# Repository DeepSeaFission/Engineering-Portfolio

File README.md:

# Engineering Portfolio - Jordan Langford

This repository contains my current engineering portfolio, including my work on power distribution system for a 1U Cubesat as the Team Lead for the University of Utah's UCubeSat Photovoltaics and Power Distribution team, a custom GPS personal project, and code demosntrating my use of complex boolean statements, GUI generation, and machine learning techniques.

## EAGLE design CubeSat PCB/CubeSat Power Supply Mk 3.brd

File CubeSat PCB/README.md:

# 1U CubeSat Power Supply - UCubeSat Collegiate Club Activity
Generated as Team Lead for the Photovoltaics and Power Distribution Team

This project was my attempt to produce a reliable 1U CubeSat Power Supply powered by two Li-Po 18650 batteries. 

## Mk 1

This PCB went through several iterations before reaching this final stage. Initially, when the UCubeSat club was just getting started and our requirements were ill-defined, I began with a dual 12V/5V power supply just to have something for the team to work on and to generate interest. That design included a boost converter to generate the 12V, since the combined voltage of the 18650 batteries was only around 8.4V at max charge. 

## Mk 2

After further design refining, we determined only a 5V rail was necessary. Intead of a buck converter that would need to operate at high efficiency across the full range of voltage the batteries would produce in series, I opted for a design relying on voltage following OpAmps following a stable 5V positive terminal voltage generated by a zener diode. The zener diode branch draws low current thanks to high resistance resistors in series with the diode. 

Unfortunately, my first iteration of this design had a few flaws. I wired the Opamp outputs together with the intention of having a combined source of power. When simulated in LTspice, this seemed to work well. However, in practice, this led to the feedback loops for each OpAmp fighting, leading to rapid overheating and failure. I also was attempting to solder USB-C ports to the PCB, which is extremely difficult to do by hand.

## Mk 3

This led to my final iteration. 

Each OpAmp was given a dedicated output line with an RLC filter, supplying 1 Amp at 5V. The connectors were removed with the intention that any power taps would just be soldered directly to the board using vias. This iteration is capable of powering every load we have planned for several hours. In the future, we believe it will require minimal modification to work with a solar power supply for recharging. 

This screenshot shows the traces for the PCB. High current traces are 2 mm thickness, most control traces are 0.2 mm.

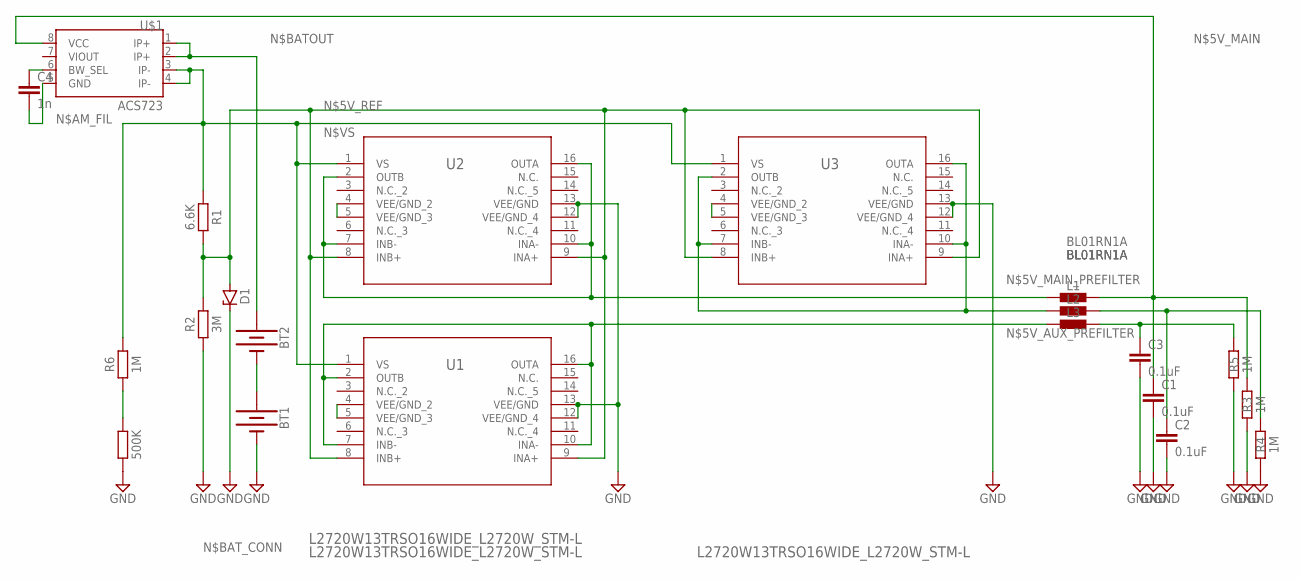
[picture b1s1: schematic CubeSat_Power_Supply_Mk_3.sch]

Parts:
BT1, BT2: BATTERY-18650; BATTERY_18650-HOLDER
C1, C2, C3: 0.1uF; CAP-PTH-SMALL-KIT
C4: 1n; CAP-PTH-SMALL-KIT
D1: ZENER-DIODESOT23; SOT23
L1, L2, L3: BL01RN1A
R1: 6.6K; RESAD724W46L381D178B
R2: 3M; RESAD724W46L381D178B
R3, R4, R5, R6: 1M; RESAD724W46L381D178B
R7: 500K; RESAD724W46L381D178B
U1, U2, U3: L2720W13TRSO16WIDE_L2720W_STM-L; SO16WIDE_L2720W_STM-L
U$1: ACS723; SO08

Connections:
GND: BT1.GND@1 (-), C1.2, C2.2, C3.2, D1.3 (C), R2.1, R3.1, R4.1, R5.1, R7.1, U1.12 (VEE/GND_4), U1.13 (VEE/GND), U2.12 (VEE/GND_4), U2.13 (VEE/GND), U3.12 (VEE/GND_4), U3.13 (VEE/GND)
unnamed: U2.4 (VEE/GND_2), U2.5 (VEE/GND_3)
unnamed: U1.4 (VEE/GND_2), U1.5 (VEE/GND_3)
unnamed: U3.4 (VEE/GND_2), U3.5 (VEE/GND_3)
unnamed: L3.1, U1.2 (OUTB), U1.7 (INB-), U1.10 (INA-), U1.16 (OUTA)
unnamed: C3.1, L3.2, R5.2
unnamed: C2.1, L2.2, R4.2
unnamed: L2.1, U3.2 (OUTB), U3.7 (INB-), U3.10 (INA-), U3.16 (OUTA)
unnamed: C1.1, L1.2, R3.2, U$1.8 (VCC)
unnamed: L1.1, U2.2 (OUTB), U2.7 (INB-), U2.10 (INA-), U2.16 (OUTA)
unnamed: D1.1 (A), R1.2, R2.2, U1.8 (INB+), U1.9 (INA+), U2.8 (INB+), U2.9 (INA+), U3.8 (INB+), U3.9 (INA+)
unnamed: C4.2, U$1.5 (GND)
N$AM_FIL: C4.1, U$1.6 (BW_SEL)
N$BATOUT: BT2.PWR@1 (+), U$1.1 (IP+), U$1.2 (IP+)
N$BAT_CONN: BT1.PWR@1 (+), BT2.GND@1 (-)
N$VMSUP: R6.1, R7.2
N$VS: R1.1, R6.2, U1.1 (VS), U2.1 (VS), U3.1 (VS), U$1.3 (IP-), U$1.4 (IP-)

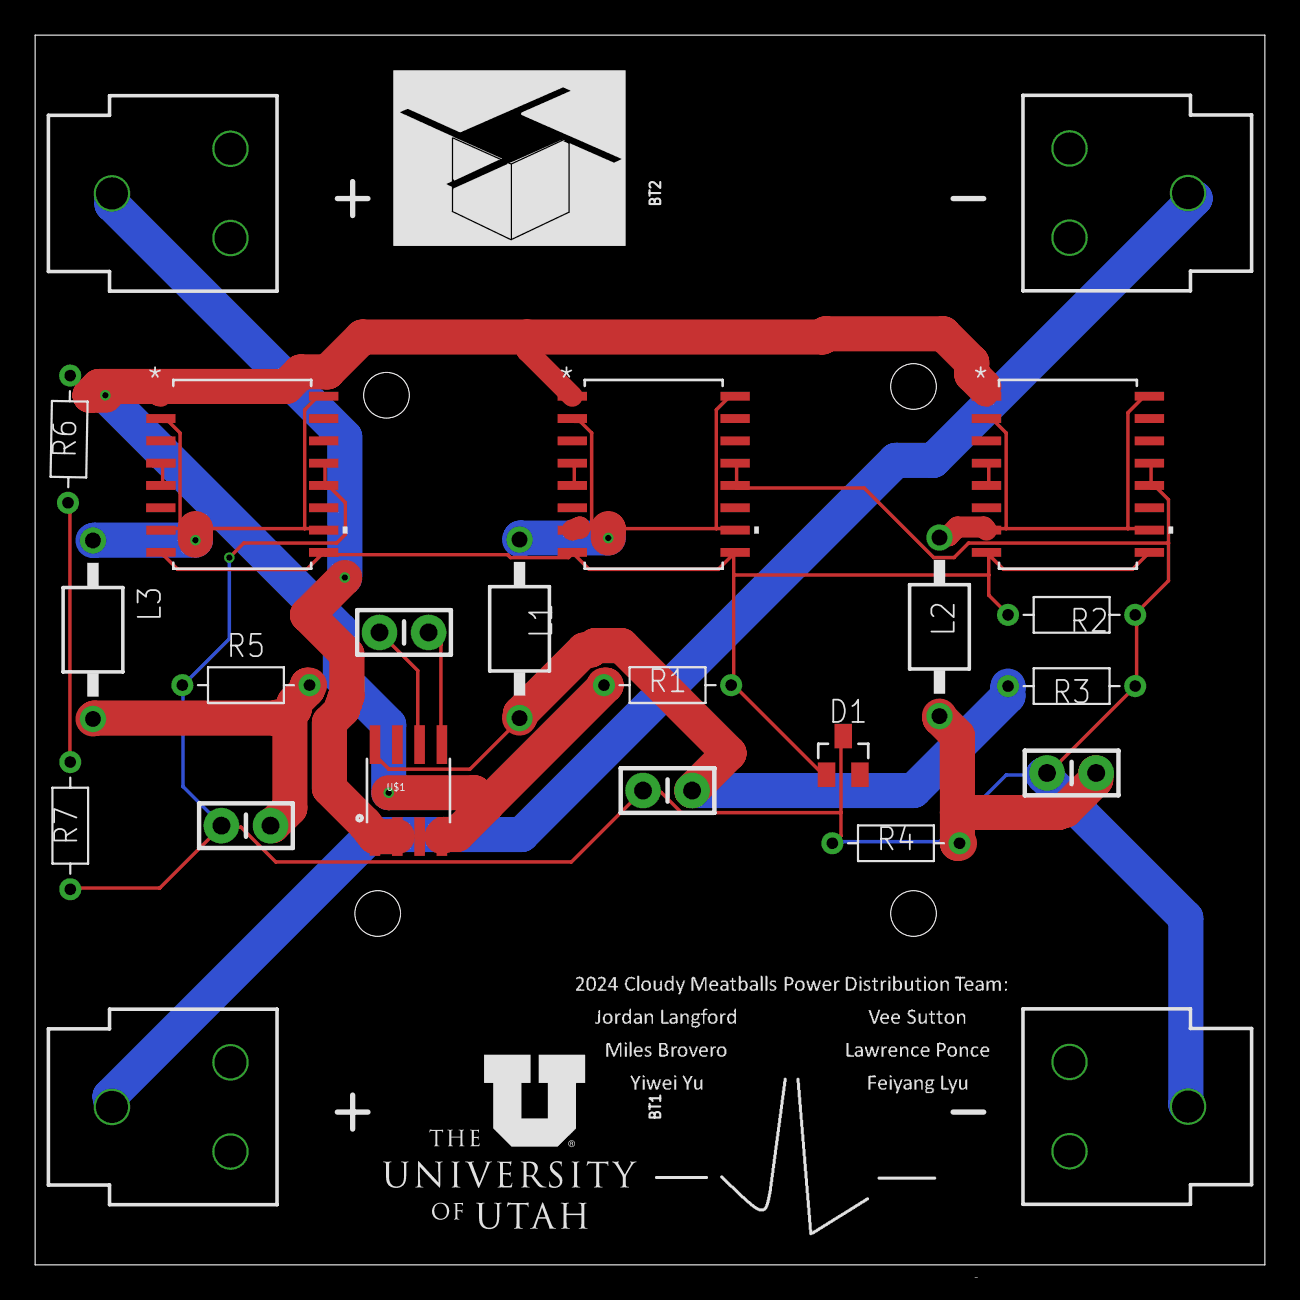
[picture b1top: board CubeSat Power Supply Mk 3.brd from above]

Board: 2 copper layers, 70.0 x 70.0 mm, 21 parts (0 on the bottom side), 17 nets.

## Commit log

2026-05-05 Added CubeSat Project Files
    CubeSat Power Supply Mk 3 files added. This is the initial release of my cubesat power supply, providing three regulated and filtered 1A 5V rails.
2026-05-05 CubeSat PS Screenshots
    Adding screenshots for use in the README
2026-05-05 Add README for CubeSat PCB power supply project
    Document the design process and iterations of the CubeSat PCB power supply project, including images of the final PCB, schematic, and traces.
2026-05-05 Revise README.md for CubeSat PCB project
    Updated image paths and improved project documentation for the 1U CubeSat Power Supply.
2026-05-05 Adding in GPS initial drawings
    Adds initial GPS engineering drawings
2026-05-05 GPS Images and Demo Video
    Adds in GPS images and demo video to support project readme
2026-05-05 Delete Images directory
    Fixing Erroneous location
2026-05-05 GPS Images and Demo Movie
    Adds in GPS images and demo movie in support of the project readme.
2026-05-06 Added lower res version
    Lower resolution demo added for embedding, hopefully
2026-05-06 Enhance README with project details and GPS functionality
    Expanded project description and added details about design and functionality.
2026-05-06 Initial Code Upload
    Adds code files aside from Machine Learning final project
2026-05-06 Machine Learning Final Project
    Adds files for my Machine Learning Final Project
2026-05-06 Integrin Brownian Motion Example
    Adds in video for integrin brownian motion
2026-05-06 Add KSP GUI
    Add KSP GUI for code folder readme
2026-05-06 Create README.md for code samples documentation
    Added README.md to document various code projects and their objectives.
2026-05-06 Change video link in README.md
    Updated video link for Integrin Brownian Motion project.
2026-05-06 Create README for engineering portfolio
    Add initial README with project details and images.

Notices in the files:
parts and their libraries:
SparkFun-Batteries: Licensing: Creative Commons ShareAlike 4.0 International - https://creativecommons.org/licenses/by-sa/4.0
COPYRIGHT: Copyright (C) 2024 Ultra Librarian. All rights reserved.
